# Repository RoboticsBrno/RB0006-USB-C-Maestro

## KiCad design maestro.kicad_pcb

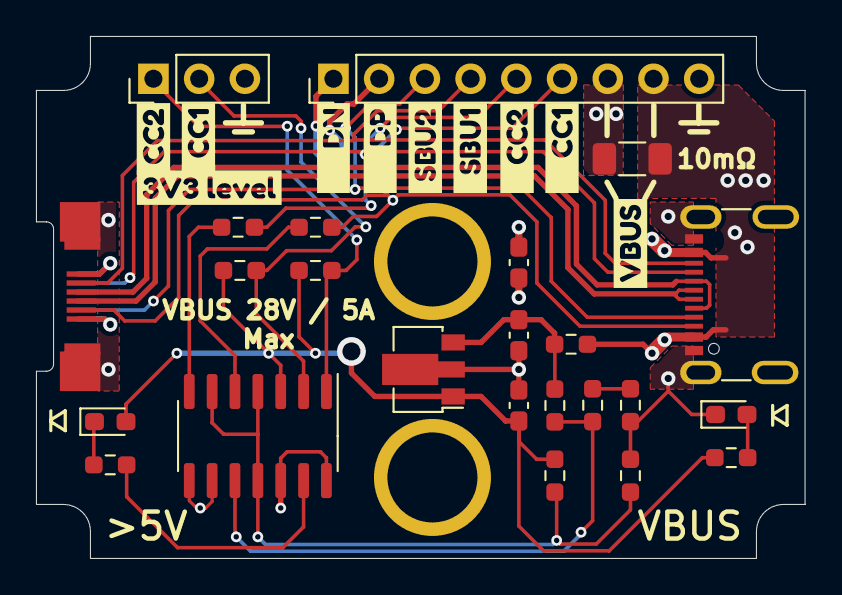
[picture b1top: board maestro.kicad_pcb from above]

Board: 2 copper layers, 42.7 x 29.0 mm, 40 parts (0 on the bottom side), 21 nets.

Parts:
C1, C2, C3: 100n; C_0603_1608Metric_Pad1.08x0.95mm_HandSolder
D1, D2: LED; LED_0603_1608Metric_Pad1.05x0.95mm_HandSolder
FB1: FerriteBead_Small; R_0603_1608Metric_Pad0.98x0.95mm_HandSolder
J1: USB_C_Receptacle; USB_C_Receptable_JAE_DX07S016JA1
J2: Conn_01x03_Male; PinHeader_1x03_P2.54mm_Vertical
J3: Conn_01x09_Male; PinHeader_1x09_P2.54mm_Vertical
J4, J5: Conn_01x01_Female; banana
P1: USB_C_Plug; HIROSE_CX60-24S-UNIT
R1, R4, R5, R6, R8, R9, R10, R11, R12: 2k; R_0603_1608Metric_Pad0.98x0.95mm_HandSolder
R2: 10m; R_1206_3216Metric_Pad1.30x1.75mm_HandSolder
R3, R7: 20k; R_0603_1608Metric_Pad0.98x0.95mm_HandSolder
T1, T2, T3, T4: Tab
U1: MCP1804x-3302xMB; SOT-89-3
U2: LM339; SOIC-14_3.9x8.7mm_P1.27mm
kibuzzard-64C4F9F7: G***; kibuzzard-64C4F9F7
kibuzzard-64C4FA01: G***; kibuzzard-64C4FA01
kibuzzard-64C4FA1B: G***; kibuzzard-64C4FA1B
kibuzzard-64C4FA2B: G***; kibuzzard-64C4FA2B
kibuzzard-64C4FA09: G***; kibuzzard-64C4FA09
kibuzzard-64C4FA25: G***; kibuzzard-64C4FA25
kibuzzard-6327537E: G***; kibuzzard-6327537E
kibuzzard-63275010: G***; kibuzzard-63275010
kibuzzard-63275379: G***; kibuzzard-63275379
kibuzzard-63275773: G***; kibuzzard-63275773

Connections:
+3V3: C3.2, D2.2 (A), R1.1, R3.2, R10.2, R11.2, U1.1 (OUT), U2.3 (V+)
/CC1: J1.A5 (CC1), J3.6, P1.A5 (CC), R5.1
/CC1_: R5.2, U2.5 (+)
/CC2: J1.B5 (CC2), J3.5, P1.B5 (VCONN), R6.1
/CC2_: R6.2, U2.7 (+)
/D+: J1.A6 (D+), J1.B6 (D+), J3.2, P1.A6 (D+)
/D-: J1.A7 (D-), J1.B7 (D-), J3.1, P1.A7 (D-)
/HV: R12.2, U2.13
/HV_: D2.1 (K), R12.1
/SBU1: J1.A8 (SBU1), J3.4, P1.A8 (SBU1)
/SBU2: J1.B8 (SBU2), J3.3, P1.B8 (SBU2)
/VBUS1: FB1.2, J1.A4 (VBUS), J1.B4 (VBUS), J3.8, R2.2
/VBUS2: C2.1, J3.7, J4.1, P1.A4 (VBUS), P1.A9 (VBUS), P1.B4 (VBUS), P1.B9 (VBUS), R2.1
/VREF: R3.1, R4.2, U2.4 (-), U2.6 (-), U2.11 (+)
GND: C1.1, C2.2, C3.1, D1.1 (K), J1.A1 (GND), J1.B1 (GND), J1.S1 (SHIELD), J2.3, J3.9, J5.1, P1.A1 (GND), P1.A12 (GND), P1.B1 (GND), P1.B12 (GND), P1.S1 (SHIELD), R4.1, R9.1, U1.2 (GND), U2.8 (-), U2.9 (+), U2.12 (V-), U2.14
unnamed: D1.2 (A), R1.2
unnamed: J2.1, R11.1, U2.1
unnamed: J2.2, R10.1, U2.2
unnamed: R7.1, R8.2, U2.10 (-)
unnamed: R8.1, R9.2
VBUS: C1.2, FB1.1, R7.2, U1.3 (IN)

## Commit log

2021-04-10 Add schematic basics
2023-11-04 Release v2
2023-11-04 Add kikit.json
